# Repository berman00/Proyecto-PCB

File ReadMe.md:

*english version below*

# Proyecto de Diseño Avanzado de circuitos impresos

por Valentin Berman

## Descripción

PCB para un microcontrolador [PIC18 45K50 de Microchip](https://www.microchip.com/en-us/product/PIC18F45K50) con una interfaz humano-máquina simple, pines de GPIO y conector USB.

Diseñado con [KiCad](https://www.kicad.org/).

## Objetivos de diseño

- Usar **partición vertical** para aumentar la compatibilidad electromagnética interna y hacer una placa más compacta. En otras palabras separar los componentes ruidosos de los componentes susceptibles colocándolos en caras opuestas del PCB.

- Elegir componentes que se puedan **soldar a mano** en la medida de lo posible.

- Diseñar **protección contra ESD** en lugares susceptibles.

- Tomar precauciones para **reducir el ruido de alimentación**.

## Guía para usar

Si tenés git instalado podes clonar el repositorio con el comando:

```shell
git clone https://github.com/berman00/Proyecto-PCB.git
```

Sino, podes descargar todos los archivos como un .zip haciendo click en el botón "Code" y luego "Descargar zip".

La repo esta organizada de la siguiente manera:

- **Datasheets:** hojas de datos referenciadas en el proyecto.

- **Entregables:** archivos entregados para evaluar el proyecto.

- **Esquemáticos de referencia:** Esquemáticos de proyectos similares.

- **Proyecto-diseño-PCB:** Proyecto de KiCad.

- **ul_PIC18LF45K50-I-P:** Modelo del micro PIC18 descargado de Microchip.

Si solo querés descargar el esquemático, o el proyecto de KiCad, los podes encontrar en los [releases](https://github.com/berman00/Proyecto-PCB/releases).

# Advanced PCB Design Project

by Valentin Berman

## Description

PCB for a [PIC18 45K50 Microcontroller by Microchip](https://www.microchip.com/en-us/product/PIC18F45K50) with a simple human-machine interface, GPIO pins, and USB connector.

Designed with [KiCad](https://www.kicad.org/).

## Design Goals

- Use **vertical partitioning** to improve internal electromagnetic compatibility and make a more compact board. In other words, separate noisy components from sensitive ones by placing them on opposite sides of the PCB.

- Choose components that can be **hand soldered** as much as possible.

- Design **ESD protection** in susceptible areas.

- Take precautions to **reduce power supply noise**.

## Usage Guide

If you have Git installed, you can clone the repository with the command:

```shell
git clone https://github.com/berman00/Proyecto-PCB.git
```

Otherwise, you can download all the files as a .zip by clicking the "Code" button and then "Download zip".

The repo is organized as follows:

- Datasheets: Data sheets referenced in the project.

- Entregables: Files submitted for project evaluation.

- Esquemáticos de referencia: Schematics from similar projects.

- Proyecto-diseño-PCB: KiCad project.

- ul_PIC18LF45K50-I-P: PIC18 microcontroller model downloaded from Microchip.

If you just want to download the schematic or the KiCad project, you can find them in the [releases](https://github.com/berman00/Proyecto-PCB/releases).

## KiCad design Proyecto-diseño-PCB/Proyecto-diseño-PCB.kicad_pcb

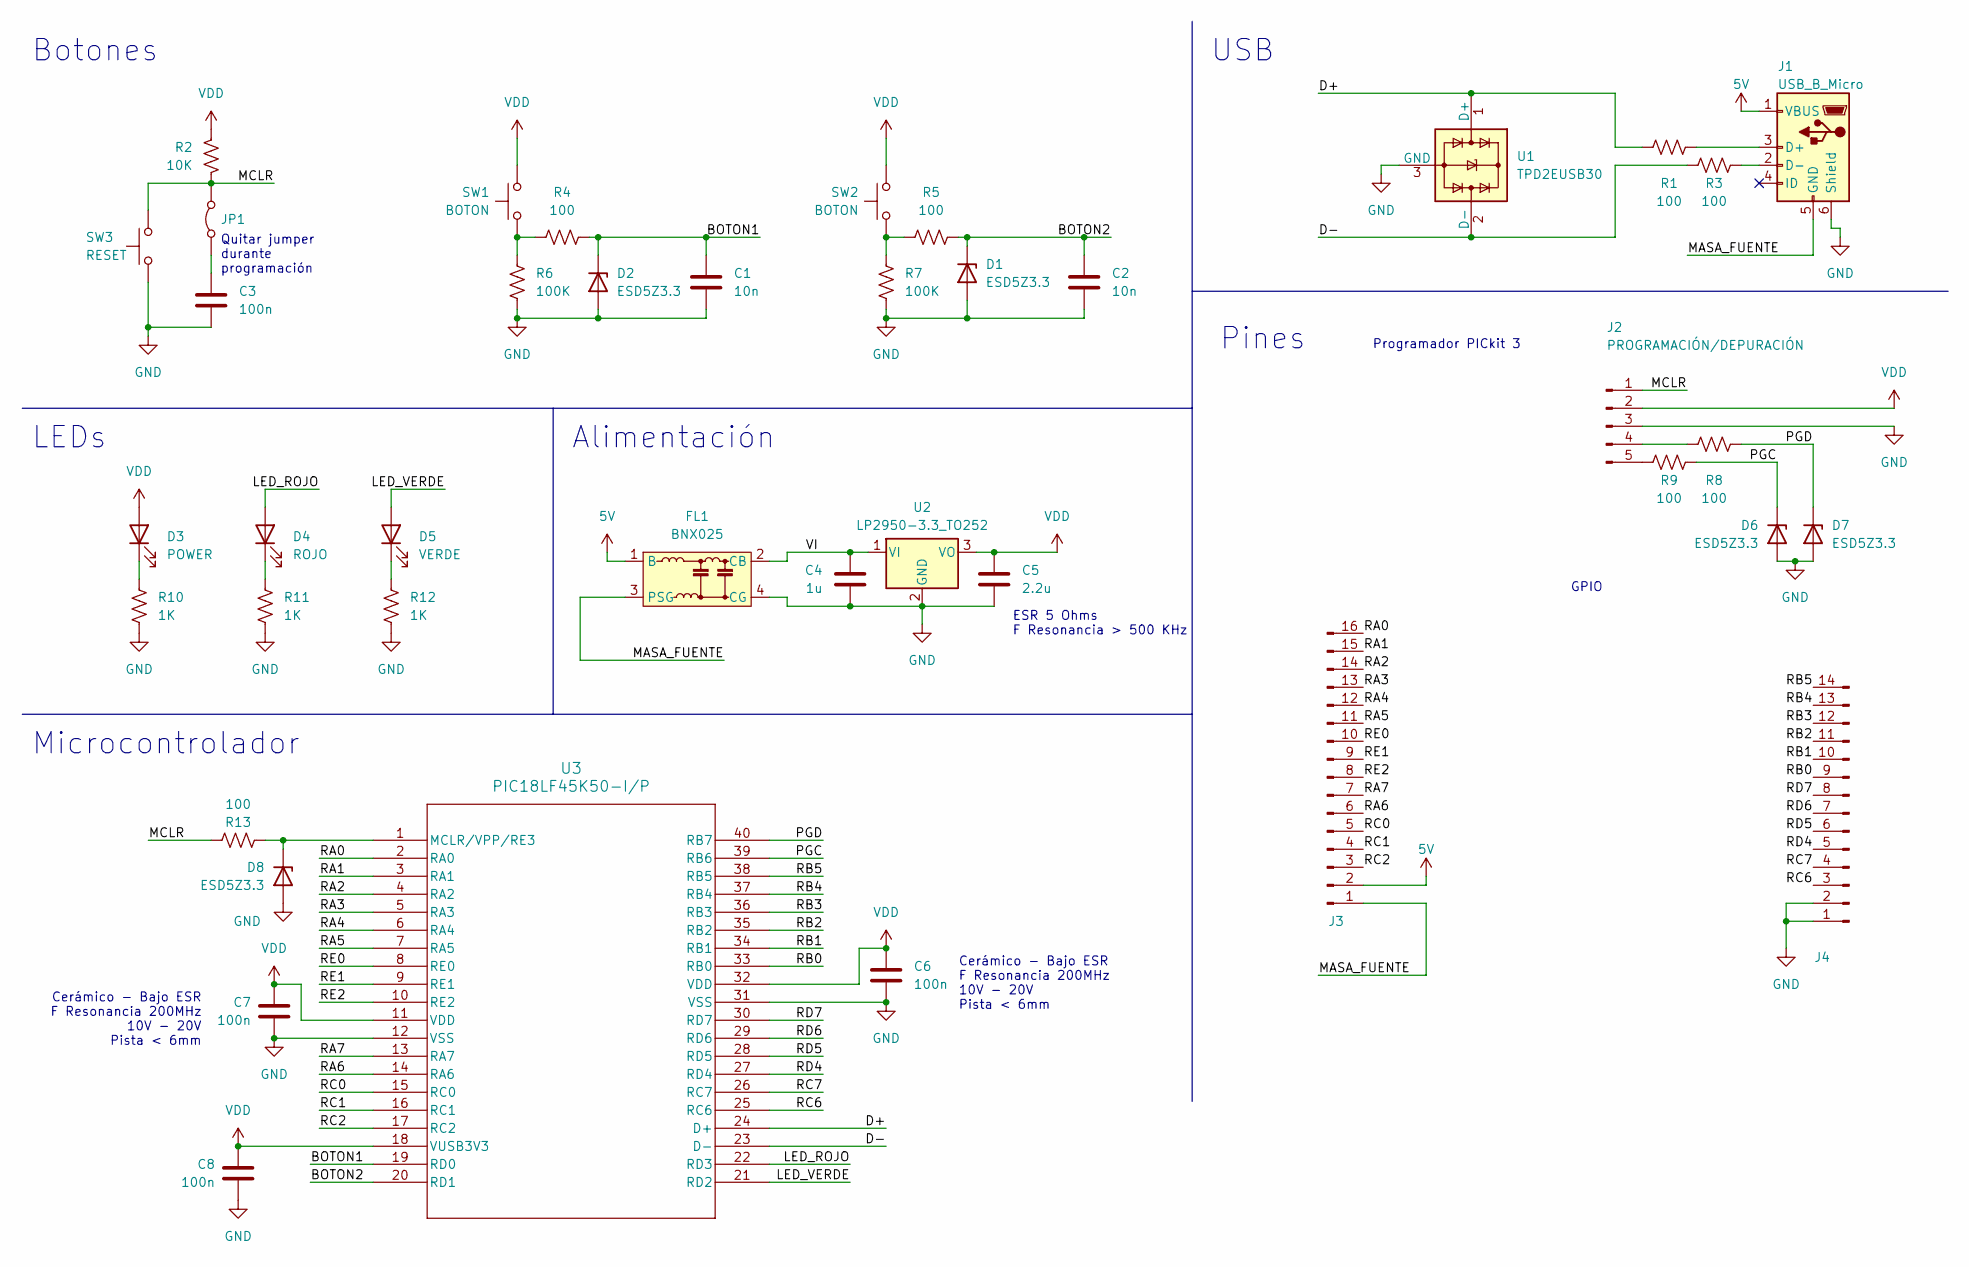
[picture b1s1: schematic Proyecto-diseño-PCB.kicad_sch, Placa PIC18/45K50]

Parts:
C1, C2: 10n; C_1206_3216Metric_Pad1.33x1.80mm_HandSolder
C3, C6, C7, C8: 100n; C_1206_3216Metric_Pad1.33x1.80mm_HandSolder
C4: 1u; C_1206_3216Metric_Pad1.33x1.80mm_HandSolder
C5: 2.2u; C_1206_3216Metric_Pad1.33x1.80mm_HandSolder
D1, D2, D6, D7, D8: ESD5Z3.3; D_SOD-523
D3: POWER; LED_D1.8mm_W3.3mm_H2.4mm
D4: ROJO; LED_D1.8mm_W3.3mm_H2.4mm
D5: VERDE; LED_D1.8mm_W3.3mm_H2.4mm
FL1: BNX025; Filter_Murata_BNX025
J1: USB_B_Micro; USB_Micro-B_Molex_47346-0001
J2: PROGRAMACIÓN/DEPURACIÓN; PinSocket_1x05_P2.54mm_Vertical
J3: LADO A; PinSocket_1x16_P2.54mm_Vertical
J4: LADO B; PinSocket_1x14_P2.54mm_Vertical
JP1: Jumper_2_Bridged; TestPoint_2Pads_Pitch2.54mm_Drill0.8mm
R1, R3, R4, R5, R8, R9, R13: 100; R_1206_3216Metric_Pad1.30x1.75mm_HandSolder
R2: 10K; R_1206_3216Metric_Pad1.30x1.75mm_HandSolder
R6, R7: 100K; R_1206_3216Metric_Pad1.30x1.75mm_HandSolder
R10, R11, R12: 1K; R_1206_3216Metric_Pad1.30x1.75mm_HandSolder
SW1: BOTON; SW_PUSH_6mm_H4.3mm
SW2: BOTON; SW_PUSH_6mm
SW3: RESET; SW_Tactile_SPST_Angled_PTS645Vx31-2LFS
U1: TPD2EUSB30; Texas_DRT-3
U2: LP2950-3.3_TO252; TO-252-2
U3: PIC18LF45K50-I/P; PDIP40_600MC_MCH

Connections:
5V: FL1.1 (B), J1.1 (VBUS), J3.2
/BOTON1: C1.1, D2.1 (K), R4.2, U3.19 (RD0)
/BOTON2: C2.1, D1.1 (K), R5.2, U3.20 (RD1)
/D+: R1.1, U1.1 (D+), U3.24 (D+)
/D-: R3.1, U1.2 (D-), U3.23 (D-)
/LED_ROJO: D4.2 (A), U3.22 (RD3)
/LED_VERDE: D5.2 (A), U3.21 (RD2)
/MASA_FUENTE: FL1.3 (PSG), J1.5 (GND), J3.1
/MCLR: J2.1, JP1.2 (B), R2.2, R13.2, SW3.2
/PGC: D6.1 (K), R9.2, U3.39 (RB6)
/PGD: D7.1 (K), R8.2, U3.40 (RB7)
/RA0: J3.16, U3.2 (RA0)
/RA1: J3.15, U3.3 (RA1)
/RA2: J3.14, U3.4 (RA2)
/RA3: J3.13, U3.5 (RA3)
/RA4: J3.12, U3.6 (RA4)
/RA5: J3.11, U3.7 (RA5)
/RA6: J3.6, U3.14 (RA6)
/RA7: J3.7, U3.13 (RA7)
/RB0: J4.9, U3.33 (RB0)
/RB1: J4.10, U3.34 (RB1)
/RB2: J4.11, U3.35 (RB2)
/RB3: J4.12, U3.36 (RB3)
/RB4: J4.13, U3.37 (RB4)
/RB5: J4.14, U3.38 (RB5)
/RC0: J3.5, U3.15 (RC0)
/RC1: J3.4, U3.16 (RC1)
/RC2: J3.3, U3.17 (RC2)
/RC6: J4.3, U3.25 (RC6)
/RC7: J4.4, U3.26 (RC7)
/RD4: J4.5, U3.27 (RD4)
/RD5: J4.6, U3.28 (RD5)
/RD6: J4.7, U3.29 (RD6)
/RD7: J4.8, U3.30 (RD7)
/RE0: J3.10, U3.8 (RE0)
/RE1: J3.9, U3.9 (RE1)
/RE2: J3.8, U3.10 (RE2)
/VI: C4.2, FL1.2 (CB), U2.1 (VI)
GND: C1.2, C2.2, C3.2, C4.1, C5.2, C6.2, C7.1, C8.1, D1.2 (A), D2.2 (A), D6.2 (A), D7.2 (A), D8.2 (A), FL1.4 (CG), J1.6 (Shield), J2.3, J4.1, J4.2, R6.2, R7.2, R10.2, R11.2, R12.2, SW3.1, U1.3 (GND), U2.2 (GND), U3.12 (VSS), U3.31 (VSS)
unnamed: D3.1 (K), R10.1
unnamed: D4.1 (K), R11.1
unnamed: D5.1 (K), R12.1
unnamed: D8.1 (K), R13.1, U3.1 (MCLR/VPP/RE3)
unnamed: J1.3 (D+), R1.2
unnamed: J1.2 (D-), R3.2
unnamed: J2.4, R8.1
unnamed: J2.5, R9.1
unnamed: C3.1, JP1.1 (A)
unnamed: R4.1, R6.1, SW1.1
unnamed: R5.1, R7.1, SW2.1
VDD: C5.1, C6.1, C7.2, C8.2, D3.2 (A), J2.2, R2.1, SW1.2, SW2.2, U2.3 (VO), U3.11 (VDD), U3.18 (VUSB3V3), U3.32 (VDD)

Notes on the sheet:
Cerámico - Bajo ESR F Resonancia 200MHz 10V - 20V Pista < 6mm
LEDs
GPIO
Botones
Microcontrolador
USB
Pines
Programador PICkit 3
Quitar jumper durante programación
ESR 5 Ohms F Resonancia > 500 KHz
Alimentación

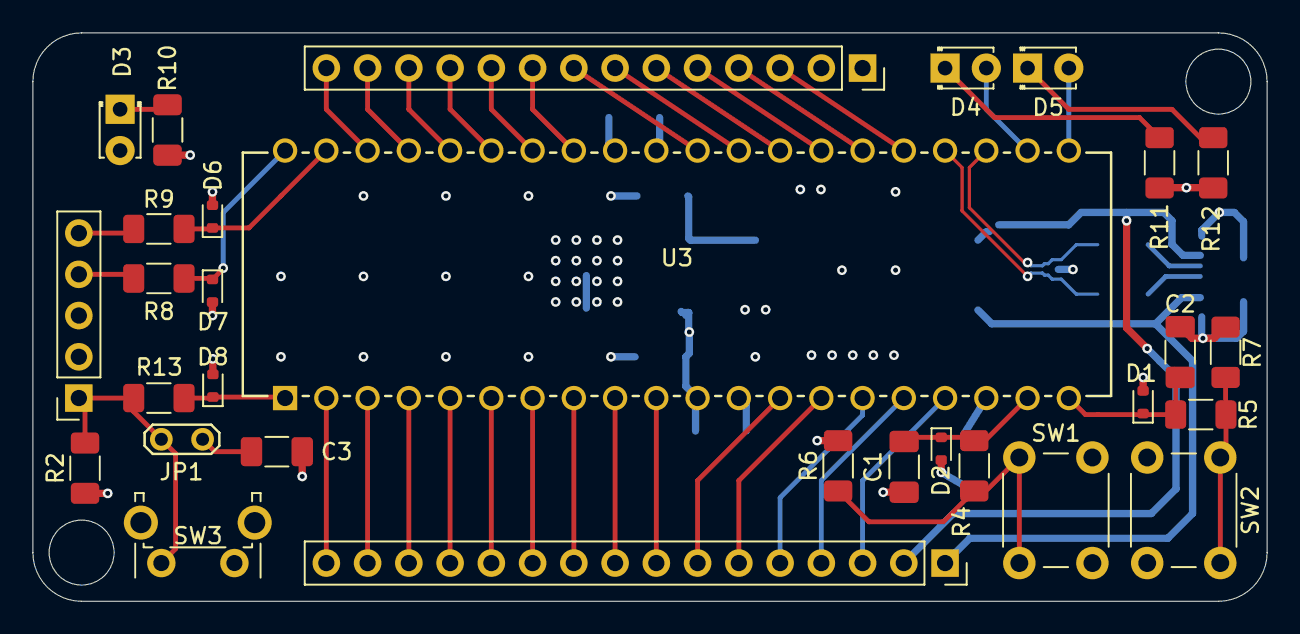
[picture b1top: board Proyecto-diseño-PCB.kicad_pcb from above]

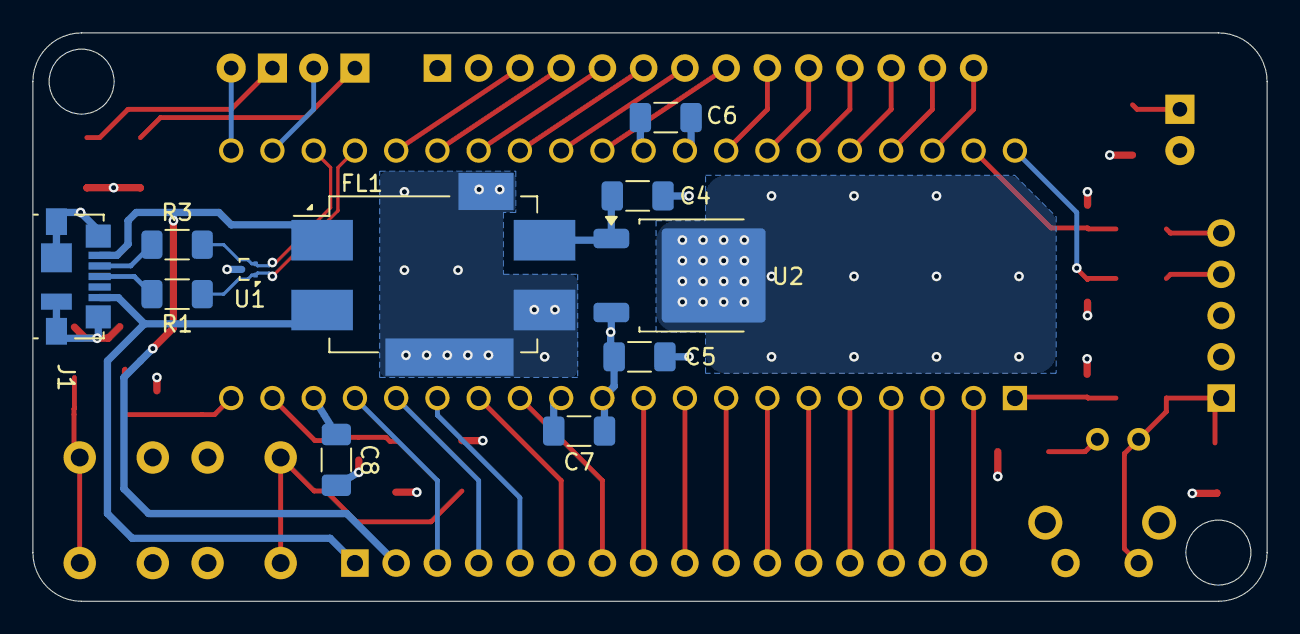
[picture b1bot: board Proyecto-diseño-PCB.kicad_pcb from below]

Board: 4 copper layers, 76.0 x 35.0 mm, 41 parts (11 on the bottom side), 51 nets.

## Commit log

2025-07-08 Commit inicial
2025-07-11 Correcciones
2025-07-11 fix: Cambio de nombre de net label
2025-07-13 fix: protección ESD
2025-07-14 gitignore
2025-07-14 esquemático v2
2025-07-15 capacitores de filtro en pines de botones de entrada
2025-07-15 Asignación de footprints
2025-07-15 Net classes
2025-07-15 Di vuelta pines para que el 1 (cuadrado) sea tierra
2025-07-15 Cambié algunos footprints y componentes
2025-07-15 Inicio PCB
2025-07-17 rest of the f-ing owl
2025-07-18 estaba haciendo pruebas de las herramientas de kicad
2025-07-22 Entrega PCB 1
2025-07-22 Modifiqué tamaño de pistas
2025-07-22 Correccion: vias separadas de pads
2025-07-22 Correccion: agregue isla para disipacion de calor
2025-07-22 Entrega PCB 2
    new file: Entregable/BERMAN_PCB_Dorso_v2.pdf
    new file: Entregable/BERMAN_PCB_Frente_v2.pdf
    renamed: Esquemático/BERMAN_Placa_45K50.pdf -> Entregable/BERMAN_Placa_45K50.pdf
    renamed: Esquemático/BERMAN_Placa_45K50_v2.pdf -> Entregable/BERMAN_Placa_45K50_v2.pdf
    deleted: Esquemático/BERMAN_PCB_Dorso.pdf
    deleted: Esquemático/BERMAN_PCB_Frente.pdf
2025-08-02 Preparado para publicar
2025-08-02 Agregué imagen y versión en ingles
2025-08-02 Error tipográfico
